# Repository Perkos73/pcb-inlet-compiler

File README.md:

# PCB INLET

Dwuwarstwowa płytka wejściowa zasilania sieciowego dla projektu Custom Step-Down PSU 230 V → 100 V.

## Stan projektu

Rewizja PCB: `PCB1-PCB-01R1`

Główny plik płytki:

`pcb-inlet.kicad_pcb`

Układ elektryczny, geometria płytki i trasowanie nie zostały zmienione. Ujednolicono nazwę pliku, strukturę repozytorium oraz automatyczne testy GitHub Actions.

## Parametry PCB

| Parametr | Wartość |
|---|---:|
| Wymiary | 105 × 70 mm |
| Liczba warstw miedzi | 2 |
| Materiał | FR-4 |
| Grubość laminatu | 1,6 mm |
| Grubość miedzi | 70 µm / 2 oz |
| Montaż elementów | THT |
| Liczba footprintów | 10 |
| Liczba przelotek | 0 |
| Otwory montażowe | 4 × 3,2 mm, NPTH, M3 |

## Funkcje płytki

Płytka zawiera:

- wejście i wyjście sieciowe na złączach śrubowych,
- bezpiecznik topikowy w przewodzie fazowym,
- warystor zabezpieczający,
- kondensator klasy X2,
- rezystor rozładowujący,
- sieci `L_IN`, `L_FUSED` i `N_IN`,
- cztery otwory montażowe M3.

## Struktura repozytorium

Najważniejsze pliki:

- `pcb-inlet.kicad_pcb` — projekt płytki KiCad,
- `.github/workflows/kicad-validate.yml` — automatyczna kontrola DRC,
- `.github/workflows/kicad-manufacturing.yml` — generowanie plików produkcyjnych,
- `.gitignore` — wykluczenie plików generowanych automatycznie,
- `README.md` — opis projektu.

## Automatyczna walidacja

Workflow `kicad-validate.yml` uruchamia się przy Pull Requestach oraz zmianach na głównej gałęzi.

Walidacja:

1. uruchamia KiCad CLI 8.0.9,
2. otwiera plik PCB,
3. wykonuje pełny raport DRC,
4. wykonuje kontrolę błędów blokujących,
5. zapisuje raporty jako artifact GitHub Actions.

Aktualny wynik kontroli bramkującej:

- 0 błędów,
- 0 niepołączonych padów.

Pełny raport może zawierać ostrzeżenia i naruszenia informacyjne wymagające ręcznej oceny.

## Pliki produkcyjne

Workflow `kicad-manufacturing.yml` jest przeznaczony do automatycznego generowania:

- warstw Gerber,
- plików wierceń,
- map wierceń,
- pliku IPC-D-356,
- raportów DRC,
- manifestu plików,
- sum kontrolnych SHA-256.

Pliki produkcyjne nie są zapisywane bezpośrednio w repozytorium. Są udostępniane w GitHub Actions jako artifact do pobrania.

## Zalecane parametry zamówienia PCB

- 2 warstwy,
- wymiary 105 × 70 mm,
- materiał FR-4,
- grubość 1,6 mm,
- miedź 2 oz,
- solder mask po obu stronach,
- opis po obu stronach,
- bez panelizacji,
- bez kontrolowanej impedancji,
- bez V-score,
- bez metalizacji krawędzi,
- bez otworów castellated.

## Bezpieczeństwo

Projekt pracuje z napięciem sieciowym.

Przed wykonaniem i uruchomieniem płytki należy sprawdzić:

- wymagane odstępy izolacyjne,
- parametry napięciowe i prądowe elementów,
- klasę bezpieczeństwa kondensatora,
- właściwy dobór bezpiecznika,
- sposób uziemienia urządzenia,
- zgodność konstrukcji z obowiązującymi wymaganiami bezpieczeństwa.

Uruchamianie układu powinno odbywać się wyłącznie przez osobę posiadającą odpowiednie doświadczenie z urządzeniami sieciowymi.

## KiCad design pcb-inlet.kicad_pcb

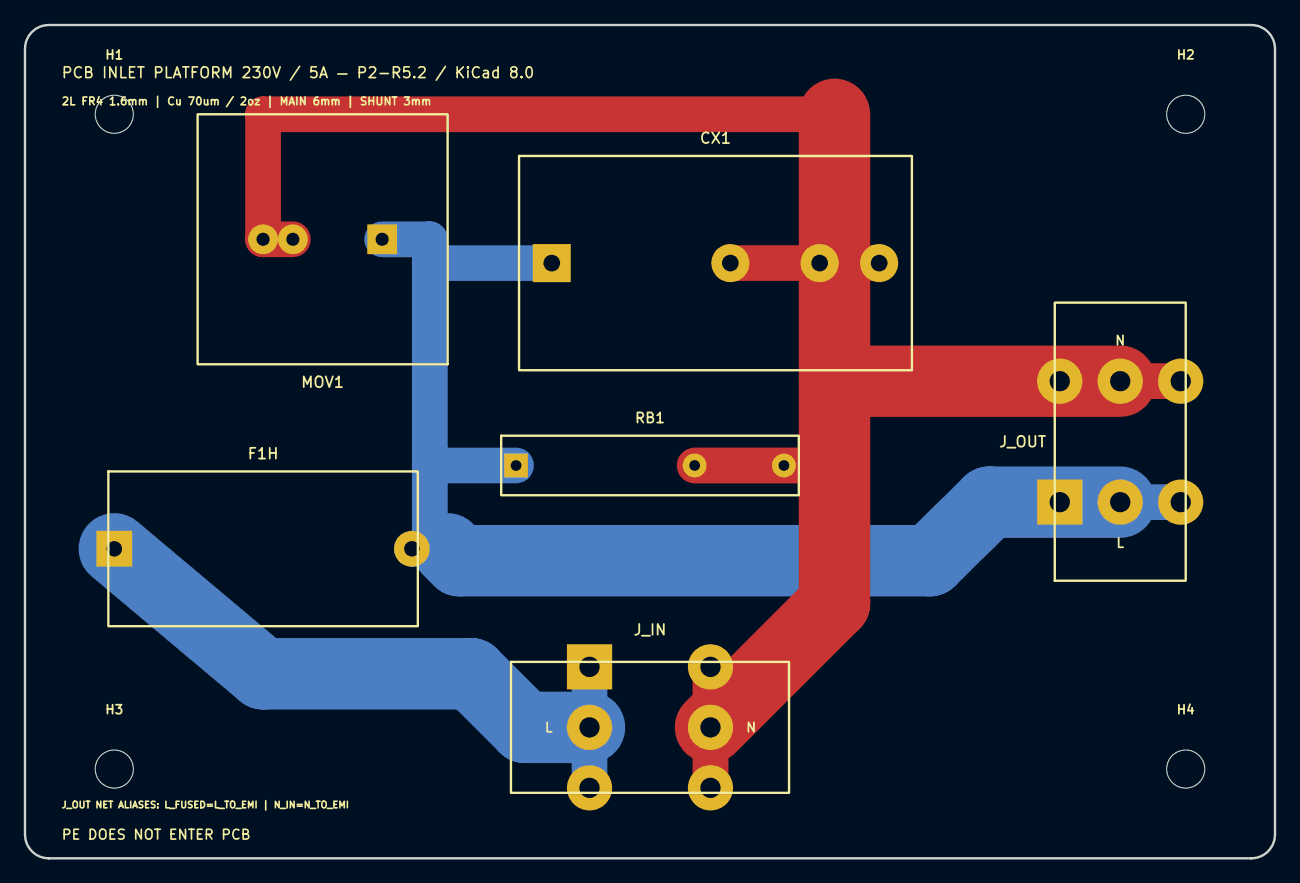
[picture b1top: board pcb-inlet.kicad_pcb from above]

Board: 2 copper layers, 105.0 x 70.0 mm, 10 parts (0 on the bottom side), 3 nets.

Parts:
CX1: Iskra KNB1532 0.22uF X2 / fitted P22.5; CX_X2_P15_P22.5_P27.5
F1H: Schurter OGN 0031.8211 / F1 T500mA; Schurter_OGN_0031.8211
H1, H2, H3, H4: NPTH 3.2 / 6mm mains clearance; MountingHole_3.2mm_M3
J_IN: Phoenix 1998784 PCV + plug 1913507; Phoenix_1998784_PCV_2P_P10.16
J_OUT: Phoenix 1998784 PCV + plug 1913507; Phoenix_1998784_PCV_2P_P10.16
MOV1: S14K320 fitted / S20 option; MOV_S14_S20_P7.5_P10
RB1: VR37 680k / fitted P15; VR37_P15_P22.5

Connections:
L_FUSED: CX1.1, F1H.2, J_OUT.1, MOV1.1, RB1.1
L_IN: F1H.1, J_IN.1
N_IN: CX1.2, J_IN.2, J_OUT.2, MOV1.2, RB1.2
